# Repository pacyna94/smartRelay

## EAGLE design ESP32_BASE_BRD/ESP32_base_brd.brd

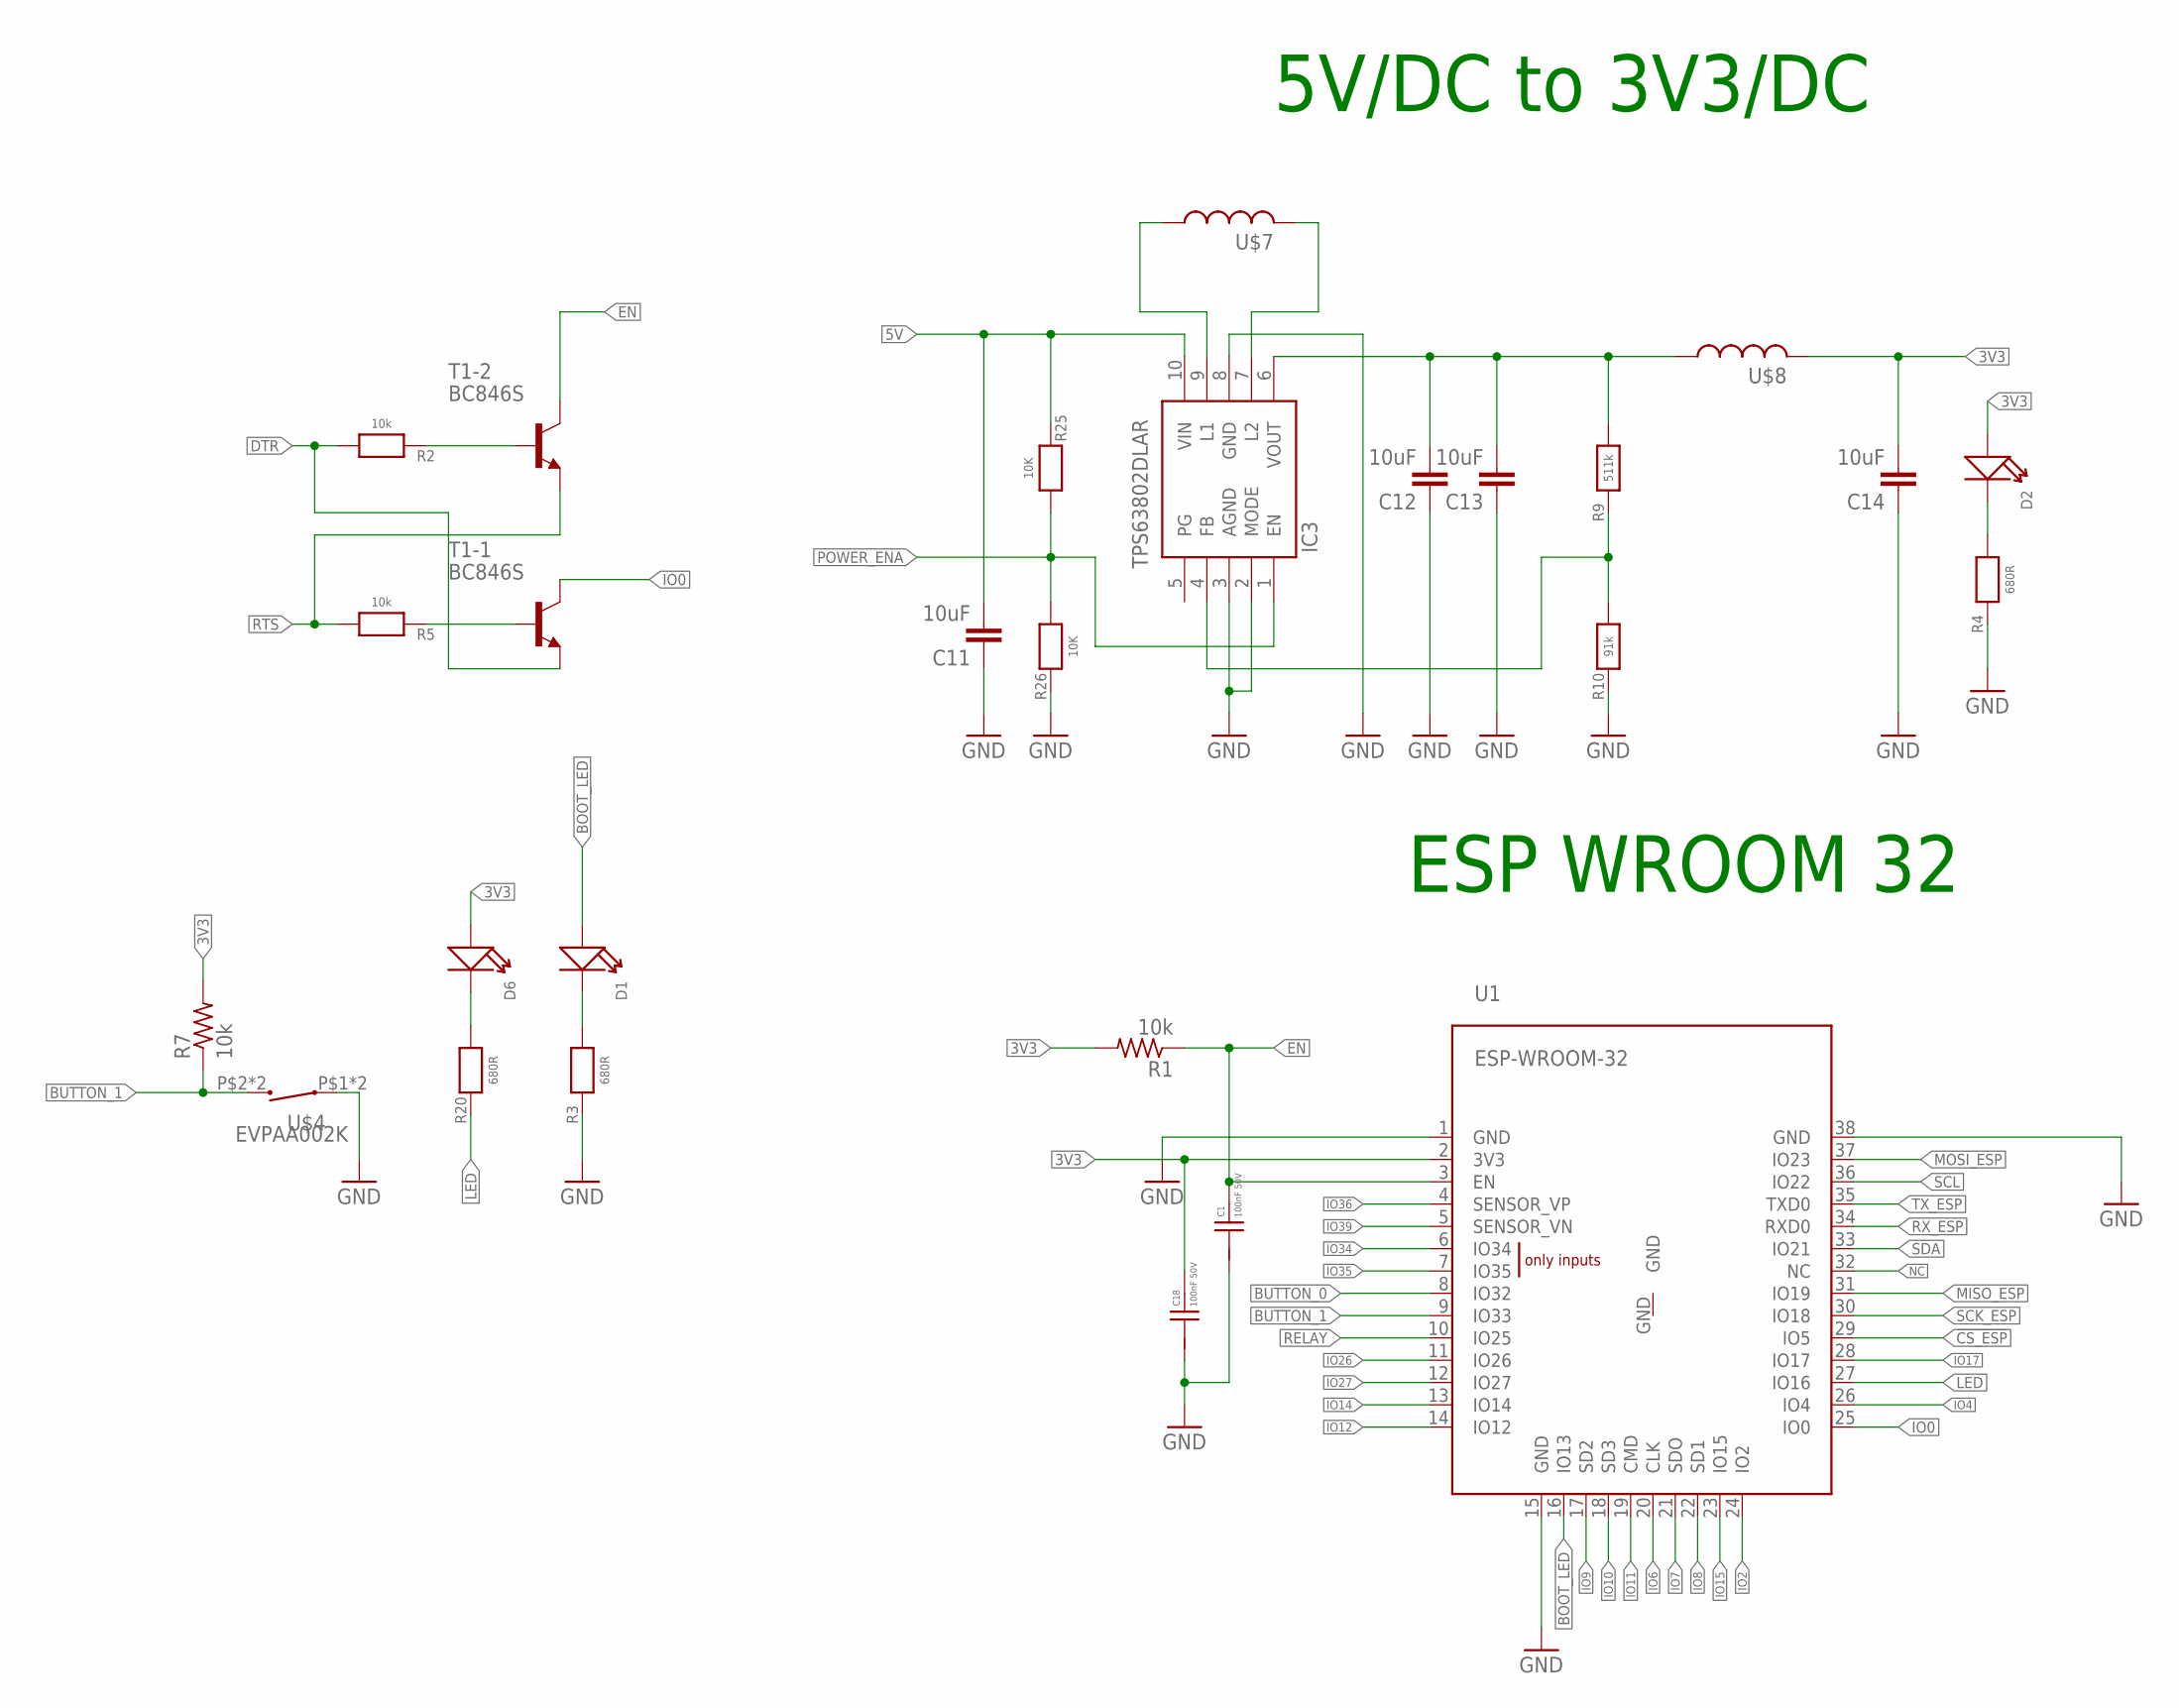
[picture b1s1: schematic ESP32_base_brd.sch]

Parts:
C1, C18: 100nF 50V; 0402
C11, C12, C13, C14: 10uF; C0603
D1, D2, D6: SMD-LED-YELLOW-DIFFUSED-PURE-WHITE(0402); LED-0402
IC3: TPS63802DLAR
R1, R7: 10k; R0805
R2, R5: 10k; 0402
R3, R4, R20: 680R; 0402
R9: 511k; 0402
R10: 91k; 0402
R25, R26: 10K; 0402
T1: BC846S; SOT363
U1: ESP-WROOM-32
U$4: EVPAA002K
U$7, U$8: INDUCTOR_2016; 2016

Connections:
3V3: C14.2, C18.2, D2.+, D6.+, R1.2, R7.2, U1.2 (3V3), U$8.2
5V: C11.2, IC3.10 (VIN), R25.1
!CS_ESP: U1.29 (IO5)
BOOT_LED: D1.+, U1.16 (IO13)
BUTTON_0: U1.8 (IO32)
BUTTON_1: R7.1, U1.9 (IO33), U$4.P$2 (2), U$4.P$4 (2)
DTR: R2.2, T1.1 (E)
EN: C1.2, R1.1, T1.3 (C), U1.3 (EN)
GND: C1.1, C11.1, C12.1, C13.1, C14.1, C18.1, IC3.2 (MODE), IC3.3 (AGND), IC3.8 (GND), R3.1, R4.1, R10.1, R26.1, U1.1 (GND), U1.15 (GND), U1.38 (GND), U$4.P$1 (1), U$4.P$3 (1)
IO0: T1.6 (C), U1.25 (IO0)
IO2: U1.24 (IO2)
IO4: U1.26 (IO4)
IO6: U1.20 (CLK)
IO7: U1.21 (SDO)
IO8: U1.22 (SD1)
IO9: U1.17 (SD2)
IO10: U1.18 (SD3)
IO11: U1.19 (CMD)
IO12: U1.14 (IO12)
IO14: U1.13 (IO14)
IO15: U1.23 (IO15)
IO17: U1.28 (IO17)
IO26: U1.11 (IO26)
IO27: U1.12 (IO27)
IO34: U1.6 (IO34)
IO35: U1.7 (IO35)
IO36: U1.4 (SENSOR_VP)
IO39: U1.5 (SENSOR_VN)
LED: R20.1, U1.27 (IO16)
MISO_ESP: U1.31 (IO19)
MOSI_ESP: U1.37 (IO23)
unnamed: R2.1, T1.5 (B)
unnamed: R5.1, T1.2 (B)
unnamed: D1.-, R3.2
unnamed: D2.-, R4.2
unnamed: IC3.9 (L1), U$7.1
unnamed: IC3.7 (L2), U$7.2
unnamed: C12.2, C13.2, IC3.6 (VOUT), R9.2, U$8.1
unnamed: IC3.4 (FB), R9.1, R10.2
unnamed: D6.-, R20.2
NC: U1.32 (NC)
POWER_ENA: IC3.1 (EN), R25.2, R26.2
RELAY: U1.10 (IO25)
RTS: R5.2, T1.4 (E)
RX_ESP: U1.34 (RXD0)
SCK_ESP: U1.30 (IO18)
SCL: U1.36 (IO22)
SDA: U1.33 (IO21)
TX_ESP: U1.35 (TXD0)

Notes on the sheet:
5V/DC to 3V3/DC
ESP WROOM 32

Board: 2 copper layers, 26 parts (0 on the bottom side), 20 nets, no tracks yet.

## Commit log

2022-02-20 add platformIO and macOS to .gitignore
2022-02-20 create base schematic ESP base brd
2022-02-20 add transistor to load program without push buttons and flip boot led
2022-02-20 remove dir ESP32_base_brd in ESP32_BASE_BRD
2022-02-20 add espframework branch and create platformIO project
2022-02-26 init Arduino freamework branch
2022-02-26 change folder name
2022-02-26 reorganization of files
2022-02-26 add vs code to gitignore

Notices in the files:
parts and their libraries:
SparkFun-Aesthetics: Licensing: CC v3.0 Share-Alike You are welcome to use this library for commercial purposes.
